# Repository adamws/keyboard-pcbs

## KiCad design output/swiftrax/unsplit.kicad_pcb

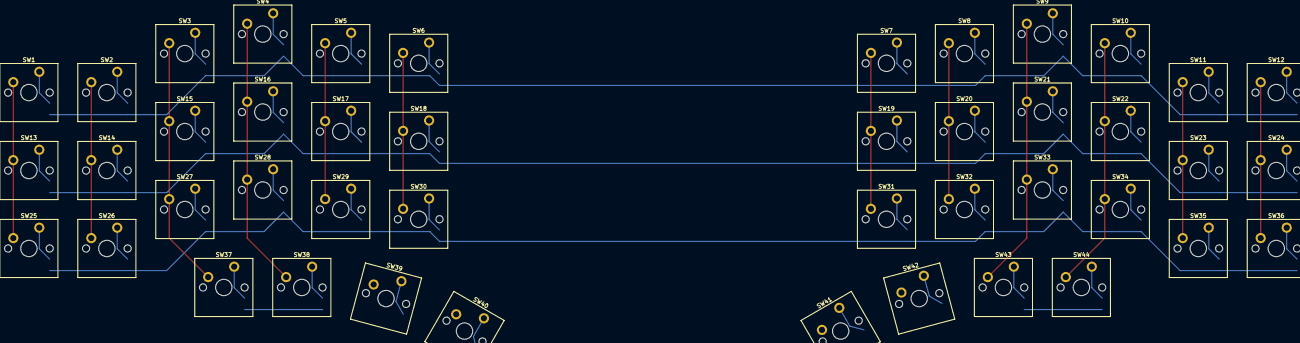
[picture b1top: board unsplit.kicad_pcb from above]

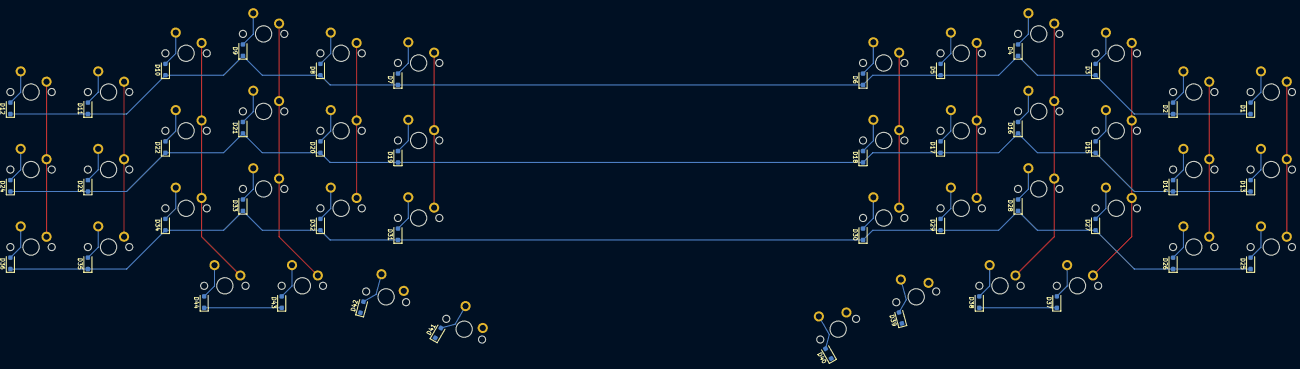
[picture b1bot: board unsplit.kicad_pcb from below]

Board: 2 copper layers, 88 parts (44 on the bottom side), 60 nets.

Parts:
D1, D2, D3, D4, D5, D6, D7, D8, D9, D10, D11, D12, D13, D14, D15, D16, D17, D18, D19, D20, D21, D22, D23, D24, D25, D26, D27, D28, D29, D30, D31, D32, D33, D34, D35, D36, D37, D38, D39, D40, D41, D42, D43, D44: D_SOD-123F
SW1, SW2, SW3, SW4, SW5, SW6, SW7, SW8, SW9, SW10, SW11, SW12, SW13, SW14, SW15, SW16, SW17, SW18, SW19, SW20, SW21, SW22, SW23, SW24, SW25, SW26, SW27, SW28, SW29, SW30, SW31, SW32, SW33, SW34, SW35, SW36, SW37, SW38, SW39, SW40, SW41, SW42, SW43, SW44: SW_Cherry_MX_PCB_1.00u

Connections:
COL0: SW1.1, SW13.1, SW25.1
COL1: SW2.1, SW14.1, SW26.1
COL2: SW3.1, SW15.1, SW27.1, SW37.1
COL3: SW4.1, SW16.1, SW28.1, SW38.1
COL4: SW5.1, SW17.1, SW29.1, SW39.1
COL5: SW6.1, SW18.1, SW30.1, SW40.1
COL6: SW7.1, SW19.1, SW31.1, SW41.1
COL7: SW8.1, SW20.1, SW32.1, SW42.1
COL8: SW9.1, SW21.1, SW33.1, SW43.1
COL9: SW10.1, SW22.1, SW34.1, SW44.1
COL10: SW11.1, SW23.1, SW35.1
COL11: SW12.1, SW24.1, SW36.1
unnamed: D1.2, SW1.2
unnamed: D2.2, SW2.2
unnamed: D3.2, SW3.2
unnamed: D4.2, SW4.2
unnamed: D5.2, SW5.2
unnamed: D6.2, SW6.2
unnamed: D7.2, SW7.2
unnamed: D8.2, SW8.2
unnamed: D9.2, SW9.2
unnamed: D10.2, SW10.2
unnamed: D11.2, SW11.2
unnamed: D12.2, SW12.2
unnamed: D13.2, SW13.2
unnamed: D14.2, SW14.2
unnamed: D15.2, SW15.2
unnamed: D16.2, SW16.2
unnamed: D17.2, SW17.2
unnamed: D18.2, SW18.2
unnamed: D19.2, SW19.2
unnamed: D20.2, SW20.2
unnamed: D21.2, SW21.2
unnamed: D22.2, SW22.2
unnamed: D23.2, SW23.2
unnamed: D24.2, SW24.2
unnamed: D25.2, SW25.2
unnamed: D26.2, SW26.2
unnamed: D27.2, SW27.2
unnamed: D28.2, SW28.2
unnamed: D29.2, SW29.2
unnamed: D30.2, SW30.2
unnamed: D31.2, SW31.2
unnamed: D32.2, SW32.2
unnamed: D33.2, SW33.2
unnamed: D34.2, SW34.2
unnamed: D35.2, SW35.2
unnamed: D36.2, SW36.2
unnamed: D37.2, SW37.2
unnamed: D38.2, SW38.2
unnamed: D39.2, SW39.2
unnamed: D40.2, SW40.2
unnamed: D41.2, SW41.2
unnamed: D42.2, SW42.2
unnamed: D43.2, SW43.2
unnamed: D44.2, SW44.2
ROW0: D1.1, D2.1, D3.1, D4.1, D5.1, D6.1, D7.1, D8.1, D9.1, D10.1, D11.1, D12.1
ROW1: D13.1, D14.1, D15.1, D16.1, D17.1, D18.1, D19.1, D20.1, D21.1, D22.1, D23.1, D24.1
ROW2: D25.1, D26.1, D27.1, D28.1, D29.1, D30.1, D31.1, D32.1, D33.1, D34.1, D35.1, D36.1
ROW3: D37.1, D38.1, D39.1, D40.1, D41.1, D42.1, D43.1, D44.1

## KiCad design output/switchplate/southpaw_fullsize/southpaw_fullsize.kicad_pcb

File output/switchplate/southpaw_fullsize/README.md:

## switchplate/southpaw_fullsize

[layout](southpaw_fullsize-kle.json) - [PCB](southpaw_fullsize.kicad_pcb)

{:loading="lazy"}

[Open in keyboard-layout-editor](http://www.keyboard-layout-editor.com/##@@_c=#777777;&=0,0&_c=#aaaaaa;&=0,1&=0,2&_x:1.25&c=#777777;&=0,4&_x:1.0&c=#cccccc;&=0,6&=0,7&=0,8&=0,9&_x:0.5&c=#aaaaaa;&=0,10&=0,11&=0,12&=0,13&_x:0.5&c=#cccccc;&=0,14&=0,15&=0,16&=0,17&_x:0.25&c=#aaaaaa;&=0,19&=0,20&=0,21;&@_y:0.25;&=1,0&=1,1&=1,2&=1,3&_x:0.25;&=1,4&_c=#cccccc;&=1,5&=1,6&=1,7&=1,8&=1,9&=1,10&=1,11&=1,12&=1,13&=1,14&=1,15&=1,16&_c=#aaaaaa&w:2;&=1,17%0A%0A%0A5,0&_x:0.25;&=1,19&=1,20&=1,21;&@_c=#cccccc;&=2,0%0A%0A%0A0,0&=2,1&=2,2&=2,3%0A%0A%0A2,0&_x:0.25&c=#aaaaaa&w:1.5;&=2,4&_c=#cccccc;&=2,5&=2,6&=2,7&=2,8&=2,9&=2,10&=2,11&=2,12&=2,13&=2,14&=2,15&=2,16&_c=#aaaaaa&w:1.5;&=2,17%0A%0A%0A6,0&_x:0.25;&=2,19&=2,20&=2,21;&@_c=#cccccc;&=3,0%0A%0A%0A0,0&=3,1&=3,2&=3,3%0A%0A%0A2,0&_x:0.25&c=#aaaaaa&w:1.75;&=3,4&_c=#cccccc;&=3,5&=3,6&=3,7&=3,8&=3,9&=3,10&=3,11&=3,12&=3,13&=3,14&=3,15&_c=#777777&w:2.25;&=3,17%0A%0A%0A6,0;&@_c=#cccccc;&=4,0%0A%0A%0A1,0&=4,1&=4,2&=4,3%0A%0A%0A3,0&_x:0.25&c=#aaaaaa&w:2.25;&=4,4%0A%0A%0A4,0&_c=#cccccc;&=4,6&=4,7&=4,8&=4,9&=4,10&=4,11&=4,12&=4,13&=4,14&=4,15&_c=#aaaaaa&w:2.75;&=4,16%0A%0A%0A7,0&_x:1.25;&=4,20;&@_c=#cccccc;&=5,0%0A%0A%0A1,0&=5,1%0A%0A%0A1,0&=5,2%0A%0A%0A3,0&=5,3%0A%0A%0A3,0&_x:0.25&c=#aaaaaa&w:1.5;&=5,4%0A%0A%0A8,0&=5,5%0A%0A%0A8,0&_w:1.5;&=5,6%0A%0A%0A8,0&_c=#cccccc&w:7;&=5,10%0A%0A%0A8,0&_c=#aaaaaa&w:1.5;&=5,14%0A%0A%0A8,0&=5,15%0A%0A%0A8,0&_w:1.5;&=5,16%0A%0A%0A8,0&_x:0.25;&=5,19&=5,20&=5,21;&@_x:4.25&y:0.25&w:1.25;&=5,4%0A%0A%0A8,1&_w:1.25;&=5,5%0A%0A%0A8,1&_w:1.25;&=5,6%0A%0A%0A8,1&_c=#cccccc&w:6.25;&=5,10%0A%0A%0A8,1&_c=#aaaaaa&w:1.25;&=5,13%0A%0A%0A8,1&_w:1.25;&=5,14%0A%0A%0A8,1&_w:1.25;&=5,15%0A%0A%0A8,1&_w:1.25;&=5,16%0A%0A%0A8,1;&@_y:-0.75&h:2;&=2,0%0A%0A%0A0,1&_x:2&h:2;&=2,3%0A%0A%0A2,1;&@_x:17.25;&=1,17%0A%0A%0A5,1&=1,18%0A%0A%0A5,1;&@_x:18&c=#777777&w:1.25&h:2&w2:1.5&h2:1&x2:-0.25;&=3,17%0A%0A%0A6,1;&@_y:-0.75&c=#aaaaaa&h:2;&=4,0%0A%0A%0A1,1&_x:2&h:2;&=4,3%0A%0A%0A3,1;&@_x:17&y:-0.25&c=#cccccc;&=3,16%0A%0A%0A6,1;&@_x:1&y:-0.75;&=5,1%0A%0A%0A1,1&=5,2%0A%0A%0A3,1;&@_x:4.5&y:-0.25&w:1.25;&=4,4%0A%0A%0A4,1&=4,5%0A%0A%0A4,1&_x:9.75&c=#aaaaaa&w:1.75;&=4,16%0A%0A%0A7,1&=4,18%0A%0A%0A7,1;&@_y:-0.5&c=#cccccc;&=4,0%0A%0A%0A1,2&_x:2;&=4,3%0A%0A%0A3,2;&@_w:2;&=5,0%0A%0A%0A1,2&_w:2;&=5,3%0A%0A%0A3,2)

{:loading="lazy"}

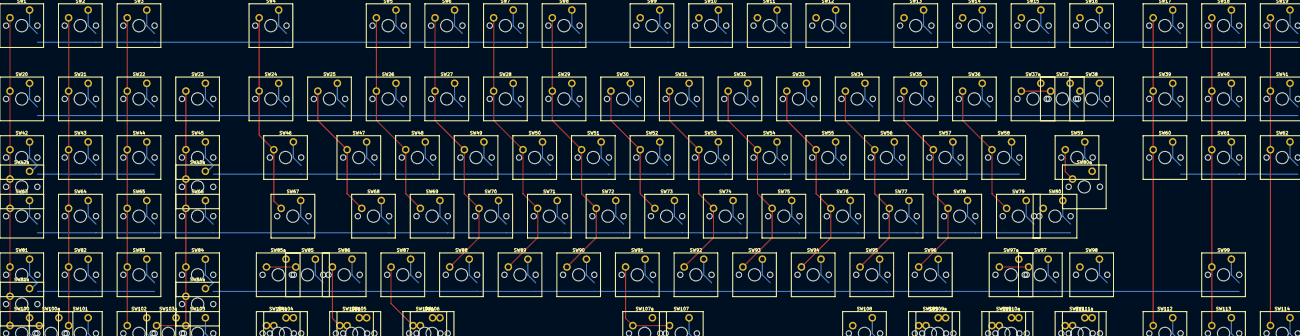
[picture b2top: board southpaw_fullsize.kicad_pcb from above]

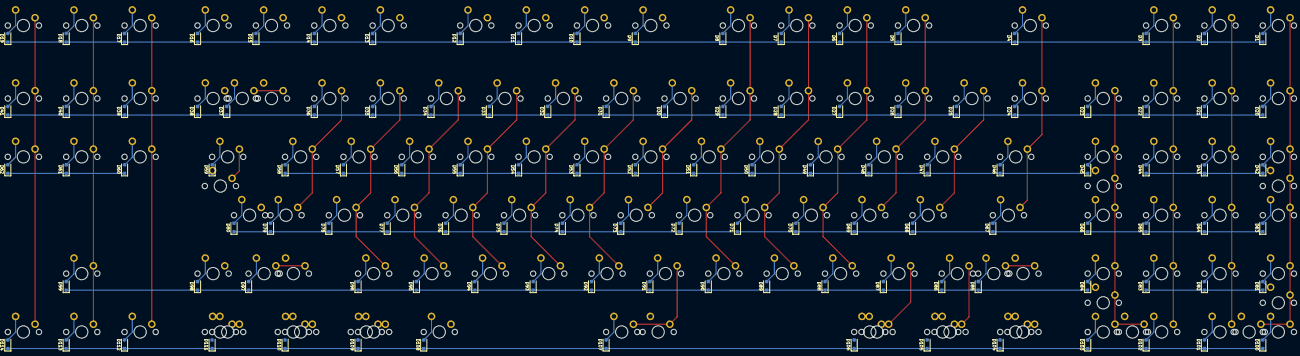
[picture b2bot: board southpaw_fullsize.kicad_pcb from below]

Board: 2 copper layers, 245 parts (114 on the bottom side), 142 nets.

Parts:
D1, D2, D3, D4, D5, D6, D7, D8, D9, D10, D11, D12, D13, D14, D15, D16, D17, D18, D19, D20, D21, D22, D23, D24, D25, D26, D27, D28, D29, D30, D31, D32, D33, D34, D35, D36, D37, D38, D39, D40, D41, D42, D43, D44, D45, D46, D47, D48, D49, D50, D51, D52, D53, D54, D55, D56, D57, D58, D59, D60, D61, D62, D63, D64, D65, D66, D67, D68, D69, D70, D71, D72, D73, D74, D75, D76, D77, D78, D79, D80, D81, D82, D83, D84, D85, D86, D87, D88, D89, D90, D91, D92, D93, D94, D95, D96, D97, D98, D99, D100, D101, D102, D103, D104, D105, D106, D107, D108, D109, D110, D111, D112, D113, D114: D_SOD-123F
SW1, SW2, SW3, SW4, SW5, SW6, SW7, SW8, SW9, SW10, SW11, SW12, SW13, SW14, SW15, SW16, SW17, SW18, SW19, SW20, SW21, SW22, SW23, SW24, SW25, SW26, SW27, SW28, SW29, SW30, SW31, SW32, SW33, SW34, SW35, SW36, SW37, SW37a, SW38, SW39, SW40, SW41, SW42, SW42a, SW43, SW44, SW45, SW45a, SW46, SW47, SW48, SW49, SW50, SW51, SW52, SW53, SW54, SW55, SW56, SW57, SW58, SW59, SW60, SW61, SW62, SW63, SW64, SW65, SW66, SW67, SW68, SW69, SW70, SW71, SW72, SW73, SW74, SW75, SW76, SW77, SW78, SW79, SW80, SW80a, SW81, SW81a, SW82, SW83, SW84, SW84a, SW85, SW85a, SW86, SW87, SW88, SW89, SW90, SW91, SW92, SW93, SW94, SW95, SW96, SW97, SW97a, SW98, SW99, SW100, SW100a, SW101, SW102, SW103, SW103a, SW104, SW104a, SW105, SW105a, SW106, SW106a, SW107, SW107a, SW108, SW109, SW109a, SW110, SW110a, SW111, SW111a, SW112, SW113, SW114: SW_Cherry_MX_PCB_1.00u

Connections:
COL0: SW1.1, SW20.1, SW42.1, SW42a.1, SW63.1, SW81.1, SW81a.1, SW100.1, SW100a.1
COL1: SW2.1, SW21.1, SW43.1, SW64.1, SW82.1, SW101.1
COL2: SW3.1, SW22.1, SW44.1, SW65.1, SW83.1, SW102.1
COL3: SW23.1, SW45.1, SW45a.1, SW66.1, SW84.1, SW84a.1, SW103.1, SW103a.1
COL4: SW4.1, SW24.1, SW46.1, SW67.1, SW85.1, SW85a.1, SW104.1, SW104a.1
COL5: SW25.1, SW47.1, SW68.1, SW86.1, SW105.1, SW105a.1
COL6: SW5.1, SW26.1, SW48.1, SW69.1, SW87.1, SW106.1, SW106a.1
COL7: SW6.1, SW27.1, SW49.1, SW70.1, SW88.1
COL8: SW7.1, SW28.1, SW50.1, SW71.1, SW89.1
COL9: SW8.1, SW29.1, SW51.1, SW72.1, SW90.1
COL10: SW9.1, SW30.1, SW52.1, SW73.1, SW91.1, SW107.1, SW107a.1
COL11: SW10.1, SW31.1, SW53.1, SW74.1, SW92.1
COL12: SW11.1, SW32.1, SW54.1, SW75.1, SW93.1
COL13: SW12.1, SW33.1, SW55.1, SW76.1, SW94.1, SW108.1
COL14: SW13.1, SW34.1, SW56.1, SW77.1, SW95.1, SW109.1, SW109a.1
COL15: SW14.1, SW35.1, SW57.1, SW78.1, SW96.1, SW110.1, SW110a.1
COL16: SW15.1, SW36.1, SW58.1, SW79.1, SW97.1, SW97a.1, SW111.1, SW111a.1
COL17: SW16.1, SW37.1, SW37a.1, SW59.1, SW80.1, SW80a.1
COL18: SW38.1, SW98.1
COL19: SW17.1, SW39.1, SW60.1, SW112.1
COL20: SW18.1, SW40.1, SW61.1, SW99.1, SW113.1
COL21: SW19.1, SW41.1, SW62.1, SW114.1
unnamed: D1.2, SW1.2
unnamed: D2.2, SW2.2
unnamed: D3.2, SW3.2
unnamed: D4.2, SW4.2
unnamed: D5.2, SW5.2
unnamed: D6.2, SW6.2
unnamed: D7.2, SW7.2
unnamed: D8.2, SW8.2
unnamed: D9.2, SW9.2
unnamed: D10.2, SW10.2
unnamed: D11.2, SW11.2
unnamed: D12.2, SW12.2
unnamed: D13.2, SW13.2
unnamed: D14.2, SW14.2
unnamed: D15.2, SW15.2
unnamed: D16.2, SW16.2
unnamed: D17.2, SW17.2
unnamed: D18.2, SW18.2
unnamed: D19.2, SW19.2
unnamed: D20.2, SW20.2
unnamed: D21.2, SW21.2
unnamed: D22.2, SW22.2
unnamed: D23.2, SW23.2
unnamed: D24.2, SW24.2
unnamed: D25.2, SW25.2
unnamed: D26.2, SW26.2
unnamed: D27.2, SW27.2
unnamed: D28.2, SW28.2
unnamed: D29.2, SW29.2
unnamed: D30.2, SW30.2
unnamed: D31.2, SW31.2
unnamed: D32.2, SW32.2
unnamed: D33.2, SW33.2
unnamed: D34.2, SW34.2
unnamed: D35.2, SW35.2
unnamed: D36.2, SW36.2
unnamed: D37.2, SW37.2, SW37a.2
unnamed: D38.2, SW38.2
unnamed: D39.2, SW39.2
unnamed: D40.2, SW40.2
unnamed: D41.2, SW41.2
unnamed: D42.2, SW42.2, SW42a.2
unnamed: D43.2, SW43.2
unnamed: D44.2, SW44.2
unnamed: D45.2, SW45.2, SW45a.2
unnamed: D46.2, SW46.2
unnamed: D47.2, SW47.2
unnamed: D48.2, SW48.2
unnamed: D49.2, SW49.2
unnamed: D50.2, SW50.2
unnamed: D51.2, SW51.2
unnamed: D52.2, SW52.2
unnamed: D53.2, SW53.2
unnamed: D54.2, SW54.2
unnamed: D55.2, SW55.2
unnamed: D56.2, SW56.2
unnamed: D57.2, SW57.2
unnamed: D58.2, SW58.2
unnamed: D59.2, SW59.2
unnamed: D60.2, SW60.2
unnamed: D61.2, SW61.2
unnamed: D62.2, SW62.2
unnamed: D63.2, SW63.2
unnamed: D64.2, SW64.2
unnamed: D65.2, SW65.2
unnamed: D66.2, SW66.2
unnamed: D67.2, SW67.2
unnamed: D68.2, SW68.2
unnamed: D69.2, SW69.2
unnamed: D70.2, SW70.2
unnamed: D71.2, SW71.2
unnamed: D72.2, SW72.2
unnamed: D73.2, SW73.2
unnamed: D74.2, SW74.2
unnamed: D75.2, SW75.2
unnamed: D76.2, SW76.2
unnamed: D77.2, SW77.2
unnamed: D78.2, SW78.2
unnamed: D79.2, SW79.2
unnamed: D80.2, SW80.2, SW80a.2
unnamed: D81.2, SW81.2, SW81a.2
unnamed: D82.2, SW82.2
unnamed: D83.2, SW83.2
unnamed: D84.2, SW84.2, SW84a.2
unnamed: D85.2, SW85.2, SW85a.2
unnamed: D86.2, SW86.2
unnamed: D87.2, SW87.2
unnamed: D88.2, SW88.2
unnamed: D89.2, SW89.2
unnamed: D90.2, SW90.2
unnamed: D91.2, SW91.2
unnamed: D92.2, SW92.2
unnamed: D93.2, SW93.2
unnamed: D94.2, SW94.2
unnamed: D95.2, SW95.2
unnamed: D96.2, SW96.2
unnamed: D97.2, SW97.2, SW97a.2
unnamed: D98.2, SW98.2
unnamed: D99.2, SW99.2
unnamed: D100.2, SW100.2, SW100a.2
unnamed: D101.2, SW101.2
unnamed: D102.2, SW102.2
unnamed: D103.2, SW103.2, SW103a.2
unnamed: D104.2, SW104.2, SW104a.2
unnamed: D105.2, SW105.2, SW105a.2
unnamed: D106.2, SW106.2, SW106a.2
unnamed: D107.2, SW107.2, SW107a.2
unnamed: D108.2, SW108.2
unnamed: D109.2, SW109.2, SW109a.2
unnamed: D110.2, SW110.2, SW110a.2
unnamed: D111.2, SW111.2, SW111a.2
unnamed: D112.2, SW112.2
unnamed: D113.2, SW113.2
unnamed: D114.2, SW114.2
ROW0: D1.1, D2.1, D3.1, D4.1, D5.1, D6.1, D7.1, D8.1, D9.1, D10.1, D11.1, D12.1, D13.1, D14.1, D15.1, D16.1, D17.1, D18.1, D19.1
ROW1: D20.1, D21.1, D22.1, D23.1, D24.1, D25.1, D26.1, D27.1, D28.1, D29.1, D30.1, D31.1, D32.1, D33.1, D34.1, D35.1, D36.1, D37.1, D38.1, D39.1, D40.1, D41.1
ROW2: D42.1, D43.1, D44.1, D45.1, D46.1, D47.1, D48.1, D49.1, D50.1, D51.1, D52.1, D53.1, D54.1, D55.1, D56.1, D57.1, D58.1, D59.1, D60.1, D61.1, D62.1
ROW3: D63.1, D64.1, D65.1, D66.1, D67.1, D68.1, D69.1, D70.1, D71.1, D72.1, D73.1, D74.1, D75.1, D76.1, D77.1, D78.1, D79.1, D80.1
ROW4: D81.1, D82.1, D83.1, D84.1, D85.1, D86.1, D87.1, D88.1, D89.1, D90.1, D91.1, D92.1, D93.1, D94.1, D95.1, D96.1, D97.1, D98.1, D99.1
ROW5: D100.1, D101.1, D102.1, D103.1, D104.1, D105.1, D106.1, D107.1, D108.1, D109.1, D110.1, D111.1, D112.1, D113.1, D114.1
